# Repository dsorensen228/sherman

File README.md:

> **Published branch snapshot:** Quiet-hours face sleep, manual wake, and clock synchronization.
> See [the main project overview](https://github.com/dsorensen228/sherman) for repository context.
> Deployment configuration in this public copy uses illustrative values.

# Project Sherman

Sherman is a palm-sized autonomous desktop exploration robot: a persistent, expressive client of Jarvis that maps a workspace, notices changes, investigates objects, and communicates mostly through animated eyes and motion.

This repository begins as an engineering plan. The current target is a `70 mm × 60 mm × 45 mm` robot built around a permanently installed Luckfox Pico Ultra W development board. That envelope is a design target and must pass the mechanical, electrical, thermal, runtime, and safety gates documented under `docs/` before it becomes a committed requirement.

## Start here

1. Read `GOALS.md` for product intent and measurable outcomes.
2. Read `docs/overall-plan.md` for the delivery strategy.
3. Use `docs/hardware/shopping-list.md` for phased procurement and `docs/hardware/display-selection.md` for the selected 1.9-inch landscape face.
4. Read `docs/architecture/system-architecture.md` and `docs/architecture/contracts.md` before changing boundaries.
5. Pick work only from a phase plan or an agent work packet.
6. Follow `AGENTS.md`, including ownership, evidence, and handoff rules.

See the [final-product render](assets/concept/sherman-final-product-render.png) and [desk-context render](assets/concept/sherman-desk-context.png) for artistic intent. They are not dimensional references.

## Hardware names

Project prose uses these two short names consistently:

- **the Pico** means the Raspberry Pi Pico 2 safety controller;
- **the Luckfox** means the Luckfox Pico Ultra W Linux computer.

Never shorten “Luckfox Pico Ultra W” to “the Pico”; that name is reserved for
the Raspberry Pi board.

## Planned repository areas

| Area | Responsibility |
| --- | --- |
| `firmware/` | Board support, device access, boot, supervisors, low-level hardware adapters |
| `core/` | Runtime lifecycle, state, event bus, safety arbitration, behavior scheduling |
| `navigation/` | Localization, occupancy grid, planning, control, docking, recovery |
| `vision/` | Camera ingestion, perception, object tracks, scene-change detection |
| `display/` | Eye renderer, animation system, display driver, visual diagnostics |
| `personality/` | Moods, needs, routines, behavior policy, Jarvis relationship |
| `websocket/` | Secure and resilient Jarvis transport |
| `proto/` | Versioned schemas and compatibility tests |
| `simulation/` | Deterministic world, robot model, sensor models, scenario runner |
| `cad/` | Chassis, mounts, serviceability, tolerances, drawings |
| `electronics/` | Power, motors, sensors, wiring, protection, board-level prototypes |
| `integration/` | Cross-subsystem bring-up, hardware-in-loop, release candidates |
| `tests/` | Shared fixtures, acceptance suites, endurance and system tests |
| `tools/` | Developer utilities, provisioning, capture, replay, analysis |
| `docs/` | Product, architecture, roadmap, decisions, safety, and operations |

## Status

Planning baseline: **v0.1**. No hardware choice beyond the Luckfox Pico Ultra W is frozen. The Waveshare 1.9-inch landscape display and exact motion/sensor/power items are selected qualification candidates, not production releases. All shopping-list entries remain candidates until their gate in `docs/hardware/bom.md` is closed with measurements or vendor documentation.

The current planning set contains six evidence-gated phase plans and subsystem-specific implementation/testing handoffs. Begin swarm execution with `docs/agents/swarm-launch-sequence.md`, not by assigning an entire phase to one agent.

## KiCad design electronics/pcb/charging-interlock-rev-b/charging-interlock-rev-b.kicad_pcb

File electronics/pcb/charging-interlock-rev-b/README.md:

# Sherman charge-interlock Rev B

Rev B replaces the rejected Rev A at **38.10 × 24.13 mm**, with the original
four Ø2.20 mm mounting holes. It reuses the ordered through-hole parts and W1
circuit. U1 now follows the manufacturer's top-view numbering and Q1 is outside
the socket footprint. No component must be installed underneath the socket.

**Status: fabrication design verified; replacement order preparation recorded in
[order-manifest.md](order-manifest.md). Physical qualification is BLOCKED-HARDWARE.**
Do not populate the received Rev A boards. Their mirrored IC footprint and
socket/Q1 interference are documented in ADR 0007.

## Assembly

All parts mount on the component side. Read the board with `REV B` at the bottom.
U1/socket notches face **left**; U1 pin 1 is **lower-left**, pin 7 lower-right,
pin 14 upper-left. Q1's flat face points **right**: top lead C, middle B,
bottom square hole E. Form Q1's outer legs gently to 2.54 mm pitch and leave
3.5 mm below its body. Follow the exact onsemi 2N3904BU pinout.

Mount R1–R7 vertically. The body goes over the square pad: right pad for R2,
upper pad for R3, left pad for all other resistors. Leave about 1.2 mm body
standoff and sleeve the folded return leads so bare leads cannot touch.
C1 is nonpolar. Cut the ordered header strip into 5/3/3 positions per board.

| Ref | Part/value per board |
| --- | --- |
| U1 | TI SN74HC08N, in TE 1-2199298-3 socket |
| Q1 | onsemi 2N3904BU |
| C1 | KEMET C315C104K5R5TA, 100 nF |
| R1, R4, R5, R6 | Yageo MFR-25, 10 kΩ |
| R2 | Yageo MFR-25, 47 kΩ |
| R3 | Yageo MFR-25, 100 kΩ |
| R7 | Yageo MFR-25, 4.7 kΩ |
| J1/J2/J3 | Samtec TSW-140-07-L-S, 5/3/3 positions |

The original parts order covers two assemblies. See [bom.csv](bom.csv) for exact
part numbers and the [Rev A purchase record](../charging-interlock-rev-a/order-manifest.md)
for quantities already ordered. The four driver-input pull-down resistors are
separate from this board. R7 already provides the SLEEP output pull-down.

## Connector map

Pins run left to right with component-side text readable; square pad is pin 1.

| Connector | 1 | 2 | 3 | 4 | 5 |
| --- | --- | --- | --- | --- | --- |
| J1 PICO | Pico pin 36, 3V3 | Pico pin 23, GND | Pico pin 5, GP3 | Pico pin 16, GP12 | Pico pin 9, GP6 / CHARGE_ABSENT |
| J2 CHARGER | #4755 VBUS | #4755 PGOOD | GND | — | — |
| J3 OUTPUTS | #2808-M CTRL | DRV8833 SLP/nSLEEP | GND | — | — |

J1.5 is an input-only observer; firmware must never drive it. J2.2 PGOOD is
active-low/open-drain. Q1 adds inhibition from raw VBUS. U1 pins 8/11 are unused
outputs; pins 9/10/12/13 are grounded. W1 voltage domains and GPIOs are unchanged.

## Receiving and qualification

1. Inspect both sides and confirm `REV B`, correct holes and undamaged copper.
   Dry-fit the socket, IC, Q1 and headers to verify the received parts fit.
2. Before population, use [netlist.csv](netlist.csv) to check same-net continuity
   and isolation among 3V3, VBUS and GND. Inspect for solder-mask/drill defects.
3. Fit resistors and C1, then the socket, Q1 and headers. Keep U1 out. Inspect
   solder joints and formed leads; verify values and no supply short.
4. With motors, motor rail, battery and driver VIN disconnected, supply
   current-limited 3.3 V at J1.1/J1.2. Confirm empty socket pin 14 is 3.3 V and
   pin 7 is GND. Remove power, then insert U1 with notch left.
5. Run the full [Section 10 truth table](../../wiring-guide.md) and
   [power-order/fault matrix](../../TESTING.md), including independent VBUS and
   PGOOD inhibition, resets and loss of power. Record measured outputs/timing in
   P3-PWR-001 before mobile installation. Qualify both SHERMAN and SPARE boards.

The board reserves Ø4.40 mm mounting hardware plus copper clearance. Larger
washers need a separate fit check. The updated enclosure model bounds are
38.10 × 24.13 × 11.78 mm including PCB, socket and IC; add underside solder,
harness plug height and service clearance in the enclosure assembly.

## Verification of the fabrication design

[validation.json](validation.json) records all 44 component pads, 47 plated
holes including 3 vias, 4 mounting holes, 9 routed nets and 2 isolated outputs.
Minimum checked body gap is 0.702 mm; minimum different-net copper clearance is
0.508 mm. KiCad 10.0.6 DRC reports zero violations and zero unconnected items.

The checks use separate mechanisms:

- Official KiCad footprint numbering/transforms and native Gerber export.
- Manufacturer pin diagrams and maximum body envelopes, including the exact
  socket and formed transistor, with foreign-hole and mounting-head access.
- A separate Gerbonara/Shapely reader reconstructs copper connectivity from the
  exported layers and plated drills against [expected-circuit.json](expected-circuit.json).
  Gerber net names are not accepted as connectivity evidence.
- Eight regression tests check the actual board and deliberately corrupt the
  layout/Gerbers. They reject Rev A, mirrored U1 pins, a transistor under the
  socket, an added copper short and a removed GP3 connection.
- OSH Park's own upload parser and rendered layer/board previews are reviewed
  against the same ZIP. Its results are in the order manifest.

These are design/fabrication checks, not a claim of measured electrical operation.
Datasheet sources and tolerances are in [manufacturer-checks.md](manufacturer-checks.md).
Evidence is under `artifacts/phase-3/P3-PWR-003/`.

## Rebuild

Use the PCB-local Python 3.13 environment, KiCad 10.0.6 and its pcbnew-enabled
Python; no repository-wide runtime is required:

```sh
cd electronics/pcb/charging-interlock-rev-b
uv venv --python 3.13 .venv
uv pip sync --python .venv/bin/python requirements.lock
.venv/bin/python build.py --kicad-cli /path/to/kicad-cli --kicad-python /path/to/kicad/python3
.venv/bin/python render-assembly.py
```

On this Mac, the build defaults locate the user-installed KiCad app.
CairoSVG on Homebrew macOS needs `DYLD_FALLBACK_LIBRARY_PATH=/opt/homebrew/lib`.
`build.py` removes a stale ZIP first and recreates it only after all checks pass.
Edit `design.json` and regenerate; do not edit generated boards or Gerber geometry.
The board's UUIDs are stable; KiCad's fabrication timestamps may change on export.
[SHA256SUMS](SHA256SUMS) identifies the exact submitted ZIP and its input files.
`vendor/` contains the licensed footprint snapshot and its checksums.

To regenerate the native populated picture with installed KiCad models:

```sh
kicad-cli pcb render -D KICAD10_3DMODEL_DIR=/path/to/3dmodels --side top --width 1500 --height 1000 --output populated.png charging-interlock-rev-b.kicad_pcb
```

The render uses stock models for illustration; acceptance uses manufacturer
maximum envelopes. `render-assembly.py` also writes the Rev B enclosure SCAD;
rebuild that STL with `models/components/build-mocks.sh` and validate the model library.

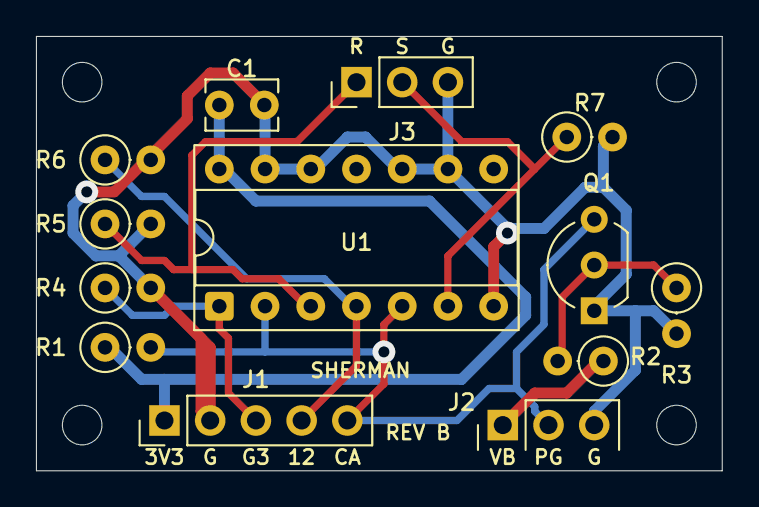
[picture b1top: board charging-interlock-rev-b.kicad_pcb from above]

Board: 2 copper layers, 38.1 x 24.1 mm, 17 parts (0 on the bottom side), 9 nets.

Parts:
C1: 100nF; C_Disc_D3.8mm_W2.6mm_P2.50mm
H1, H2, H3, H4: MountingHole_2.2mm_M2
J1: PICO; PinHeader_1x05_P2.54mm_Vertical
J2: CHARGER; PinHeader_1x03_P2.54mm_Vertical_OpenSilk
J3: OUTPUTS; PinHeader_1x03_P2.54mm_Vertical
Q1: 2N3904BU; TO-92_Inline_Wide
R1, R4, R5, R6: 10k; R_Axial_DIN0207_L6.3mm_D2.5mm_P2.54mm_Vertical
R2: 47k; R_Axial_DIN0207_L6.3mm_D2.5mm_P2.54mm_Vertical
R3: 100k; R_Axial_DIN0207_L6.3mm_D2.5mm_P2.54mm_Vertical
R7: 4.7k; R_Axial_DIN0207_L6.3mm_D2.5mm_P2.54mm_Vertical
U1: SN74HC08N; DIP-14_W7.62mm_Socket

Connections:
3V3: C1.1, J1.1, R1.1, U1.14
CHARGE_ABSENT: J1.5, J2.2, Q1.3, R1.2, U1.2, U1.5
GND: C1.2, J1.2, J2.3, J3.3, Q1.1, R3.2, R4.2, R5.2, R6.2, R7.2, U1.7, U1.9, U1.10, U1.12, U1.13
GP3: J1.3, R4.1, U1.1
GP12: J1.4, R6.1, U1.4
QBASE: Q1.2, R2.2, R3.1
RAIL_EN: J3.1, R5.1, U1.3
SLEEP_EN: J3.2, R7.1, U1.6
VBUS: J2.1, R2.1

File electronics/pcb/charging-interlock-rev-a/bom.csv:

references,quantity,value,footprint,manufacturer_part,notes
U1,1,SN74HC08N,DIP-14_W7.62mm_Socket,Texas Instruments SN74HC08N,"Quad 2-input AND gate, TI SN74HC08N"
Q1,1,2N3904BU,TO-92_Inline,onsemi 2N3904BU,"onsemi 2N3904BU; pin 1 E, 2 B, 3 C"
C1,1,100nF,C_Disc_D5.0mm_W2.5mm_P2.54mm,KEMET C315C104K5R5TA or equivalent X7R,100 nF X7R bypass capacitor
R1,1,10k,R_Axial_Vertical_P2.54mm,1% axial through-hole resistor,CHARGE_ABSENT pull-up
R2,1,47k,R_Axial_Vertical_P2.54mm,1% axial through-hole resistor,VBUS-to-Q1 base resistor
R3,1,100k,R_Axial_Vertical_P2.54mm,1% axial through-hole resistor,Q1 base-emitter pull-down
R4,1,10k,R_Axial_Vertical_P2.54mm,1% axial through-hole resistor,GP3 request pull-down
R5,1,10k,R_Axial_Vertical_P2.54mm,1% axial through-hole resistor,Motor-gate output pull-down
R6,1,10k,R_Axial_Vertical_P2.54mm,1% axial through-hole resistor,GP12 request pull-down
R7,1,4.7k,R_Axial_Vertical_P2.54mm,1% axial through-hole resistor,DRV8833 sleep output pull-down
J1,1,PICO,PinHeader_1x05_P2.54mm_Vertical,2.54 mm breakaway male header,"Pico harness: 3V3, GND, GP3, GP12, CHARGE_ABSENT/GP6"
J2,1,CHARGER,PinHeader_1x03_P2.54mm_Vertical,2.54 mm breakaway male header,"Adafruit #4755 harness: VBUS, PGOOD, GND"
J3,1,OUTPUTS,PinHeader_1x03_P2.54mm_Vertical,2.54 mm breakaway male header,"Outputs: #2808-M CTRL, DRV8833 SLP, GND"
U1-SOCKET,1,14-pin DIP socket,DIP-14_W7.62mm_Socket,TE 1-2199298-3,"Socket for U1; install socket, then IC"

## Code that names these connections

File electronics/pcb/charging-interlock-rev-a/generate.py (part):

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        ), "DRV8833 sleep output pull-down"),
        Component("J1", "PICO", "PinHeader_1x05_P2.54mm_Vertical", tuple(
            p("J1", pin, 250 + (pin - 1) * 100, 820, net, header=True)
            for pin, net in enumerate(("3V3", "GND", "GP3", "GP12", "CHARGE_ABSENT"), 1)
        ), "Pico harness: 3V3, GND, GP3, GP12, CHARGE_ABSENT/GP6"),
        Component("J2", "CHARGER", "PinHeader_1x03_P2.54mm_Vertical", tuple(
            p("J2", pin, 1050 + (pin - 1) * 100, 820, net, header=True)
            for pin, net in enumerate(("VBUS", "CHARGE_ABSENT", "GND"), 1)
        ), "Adafruit #4755 harness: VBUS, PGOOD, GND"),
        Component("J3", "OUTPUTS", "PinHeader_1x03_P2.54mm_Vertical", tuple(
            p("J3", pin, 550 + (pin - 1) * 100, 110, net, header=True)
            for pin, net in enumerate(("RAIL_EN", "SLEEP_EN", "GND"), 1)
        ), "Outputs: #2808-M CTRL, DRV8833 SLP, GND"),
    ]

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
